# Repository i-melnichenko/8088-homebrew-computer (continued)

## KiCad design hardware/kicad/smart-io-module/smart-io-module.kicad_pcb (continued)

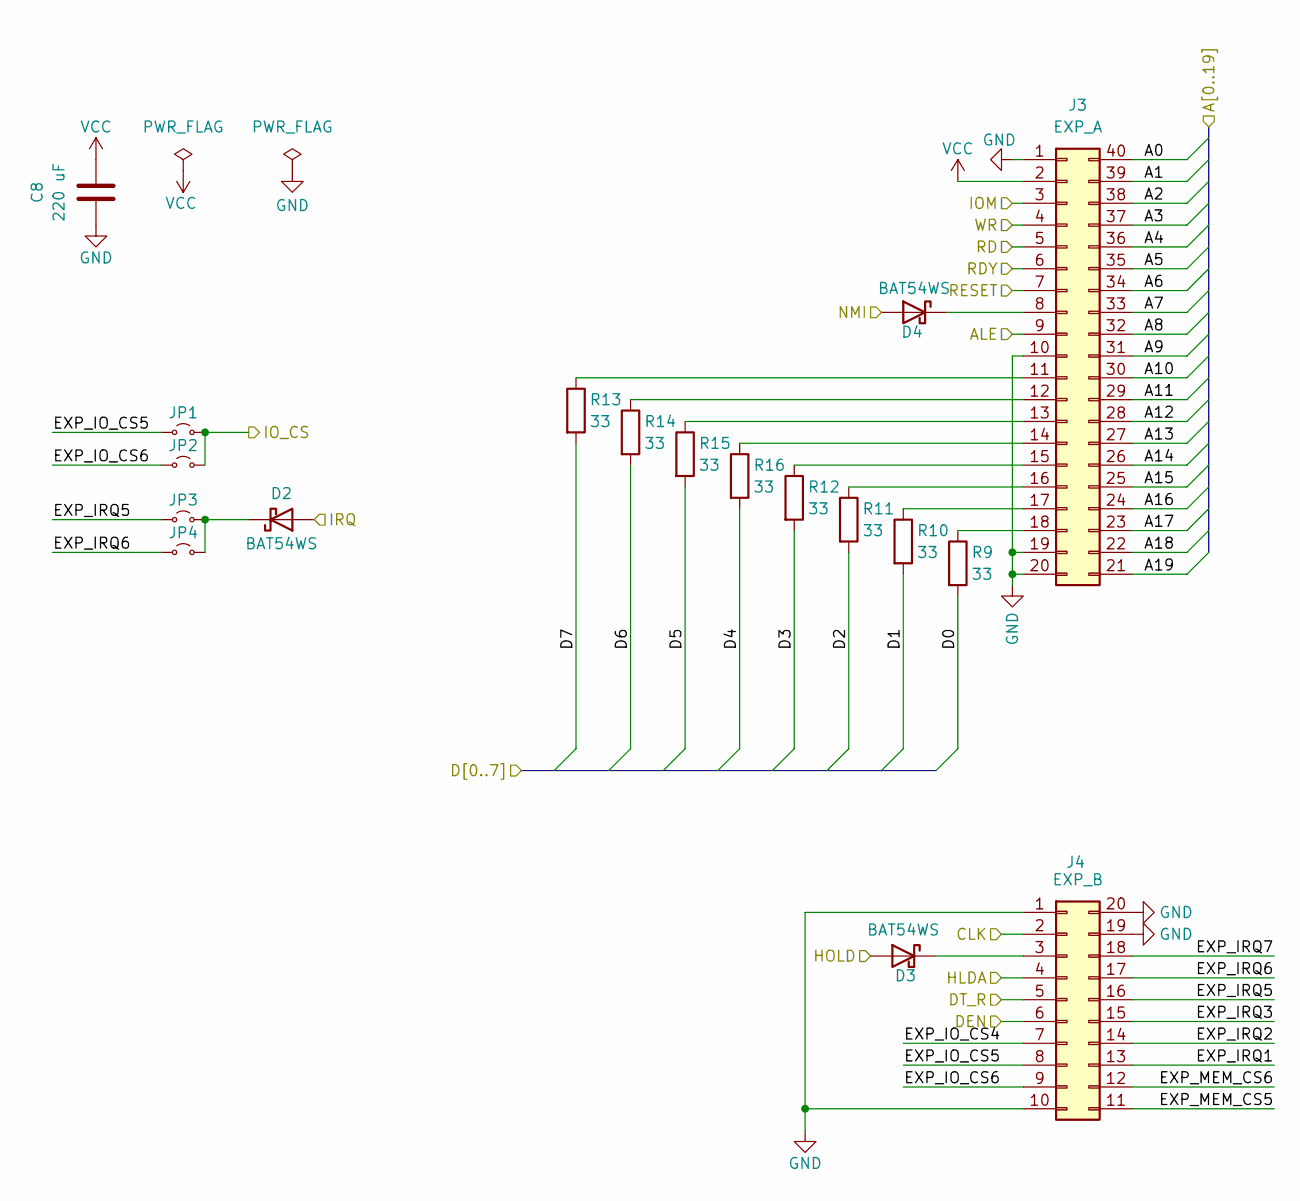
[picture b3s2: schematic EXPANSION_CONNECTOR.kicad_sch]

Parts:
C8: 220 uF; CP_Radial_D5.0mm_P2.00mm
D2, D3, D4: BAT54WS; D_SOD-323
J3: EXP_A; PinHeader_2x20_P2.54mm_Horizontal
J4: EXP_B; PinHeader_2x10_P2.54mm_Horizontal
JP1, JP2, JP3, JP4: Jumper_2_Small_Open; SolderJumper-2_P1.3mm_Open_Pad1.0x1.5mm
R9, R10, R11, R12, R13, R14, R15, R16: 33; R_0805_2012Metric

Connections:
/A0: J3.40; also elsewhere on the board
/A1: J3.39; also elsewhere on the board
/A2: J3.38; also elsewhere on the board
/A3: J3.37
/A4: J3.36
/A5: J3.35
/A6: J3.34
/A7: J3.33
/A8: J3.32
/A9: J3.31
/A10: J3.30
/A11: J3.29
/A12: J3.28
/A13: J3.27
/A14: J3.26
/A15: J3.25
/A16: J3.24
/A17: J3.23
/A18: J3.22
/A19: J3.21
/D0: R9.2; also elsewhere on the board
/D1: R10.2; also elsewhere on the board
/D2: R11.2; also elsewhere on the board
/D3: R12.2; also elsewhere on the board
/D4: R16.2; also elsewhere on the board
/D5: R15.2; also elsewhere on the board
/D6: R14.2; also elsewhere on the board
/D7: R13.2; also elsewhere on the board
/EXPANSION CONNECTOR/ALE: J3.9
/EXPANSION CONNECTOR/CLK: J4.2
/EXPANSION CONNECTOR/DEN: J4.6
/EXPANSION CONNECTOR/DT_R: J4.5
/EXPANSION CONNECTOR/EXP_IO_CS4: J4.7
/EXPANSION CONNECTOR/EXP_IO_CS5: J4.8, JP1.1 (A)
/EXPANSION CONNECTOR/EXP_IO_CS6: J4.9, JP2.1 (A)
/EXPANSION CONNECTOR/EXP_IRQ1: J4.13
/EXPANSION CONNECTOR/EXP_IRQ2: J4.14
/EXPANSION CONNECTOR/EXP_IRQ3: J4.15
/EXPANSION CONNECTOR/EXP_IRQ5: J4.16, JP3.1 (A)
/EXPANSION CONNECTOR/EXP_IRQ6: J4.17, JP4.1 (A)
/EXPANSION CONNECTOR/EXP_IRQ7: J4.18
/EXPANSION CONNECTOR/EXP_MEM_CS5: J4.11
/EXPANSION CONNECTOR/EXP_MEM_CS6: J4.12
/EXPANSION CONNECTOR/HOLD: D3.2 (A); also elsewhere on the board
/EXPANSION CONNECTOR/IOM: J3.3
/EXPANSION CONNECTOR/IRQ: D2.2 (A); also elsewhere on the board
/EXPANSION CONNECTOR/NMI: D4.2 (A); also elsewhere on the board
/EXPANSION CONNECTOR/RDY: J3.6
/HLDA: J4.4; also elsewhere on the board
/IO_CS: JP1.2 (B), JP2.2 (B); also elsewhere on the board
/RD: J3.5; also elsewhere on the board
/RESET: J3.7; also elsewhere on the board
/WR: J3.4; also elsewhere on the board
GND: C8.2, J3.1, J3.10, J3.19, J3.20, J4.1, J4.10, J4.19, J4.20; also elsewhere on the board
unnamed: D2.1 (K), JP3.2 (B), JP4.2 (B)
unnamed: D3.1 (K), J4.3
unnamed: D4.1 (K), J3.8
unnamed: J3.11, R13.1
unnamed: J3.12, R14.1
unnamed: J3.13, R15.1
unnamed: J3.14, R16.1
unnamed: J3.15, R12.1
unnamed: J3.16, R11.1
unnamed: J3.17, R10.1
unnamed: J3.18, R9.1
VCC: C8.1, J3.2; also elsewhere on the board

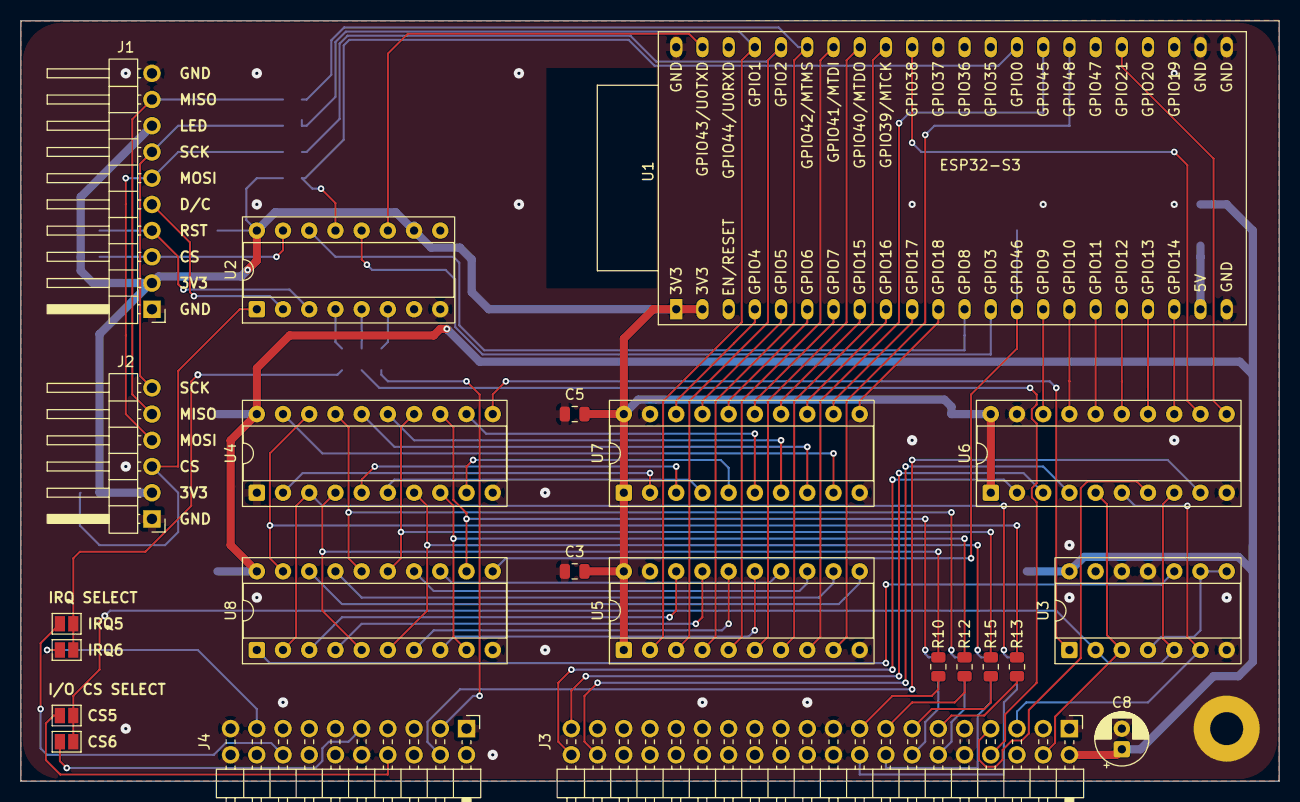
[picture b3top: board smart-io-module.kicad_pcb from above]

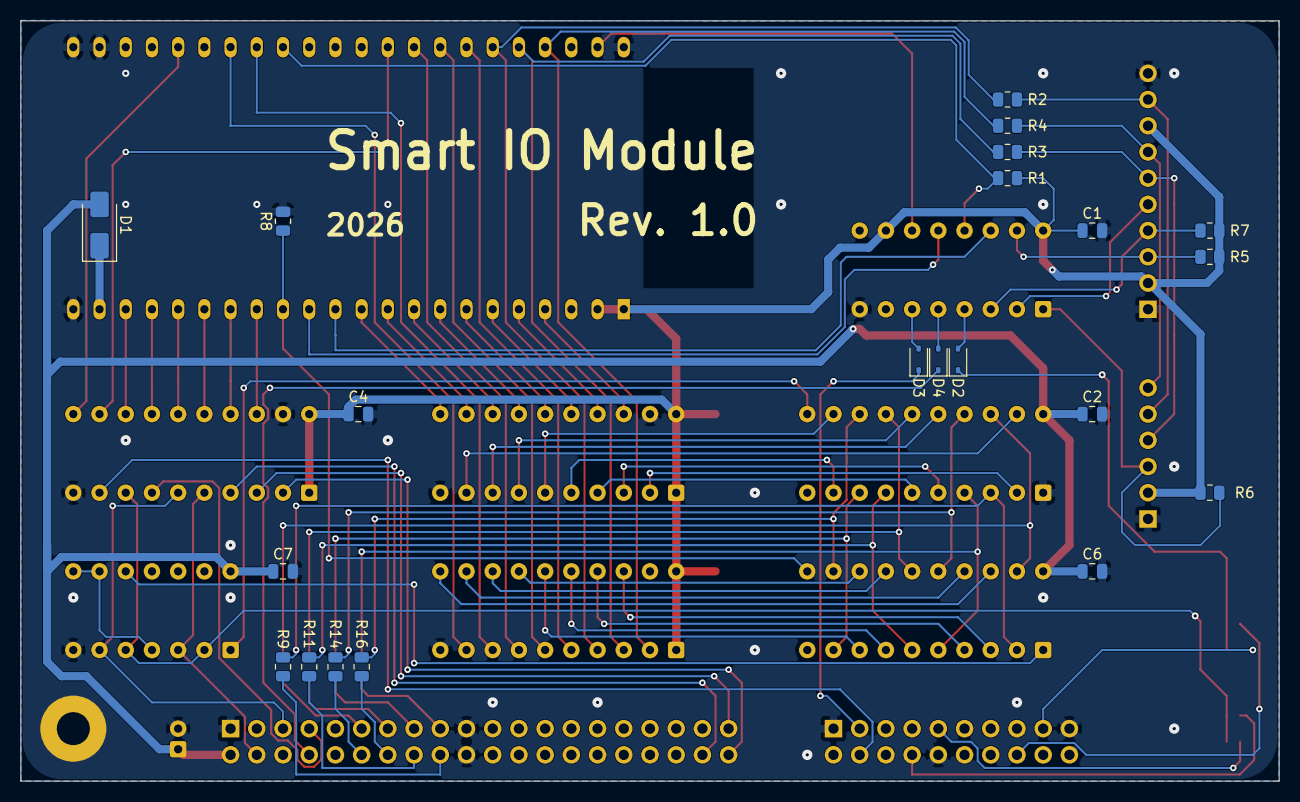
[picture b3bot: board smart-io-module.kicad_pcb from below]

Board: 2 copper layers, 121.9 x 73.7 mm, 45 parts (21 on the bottom side), 93 nets.

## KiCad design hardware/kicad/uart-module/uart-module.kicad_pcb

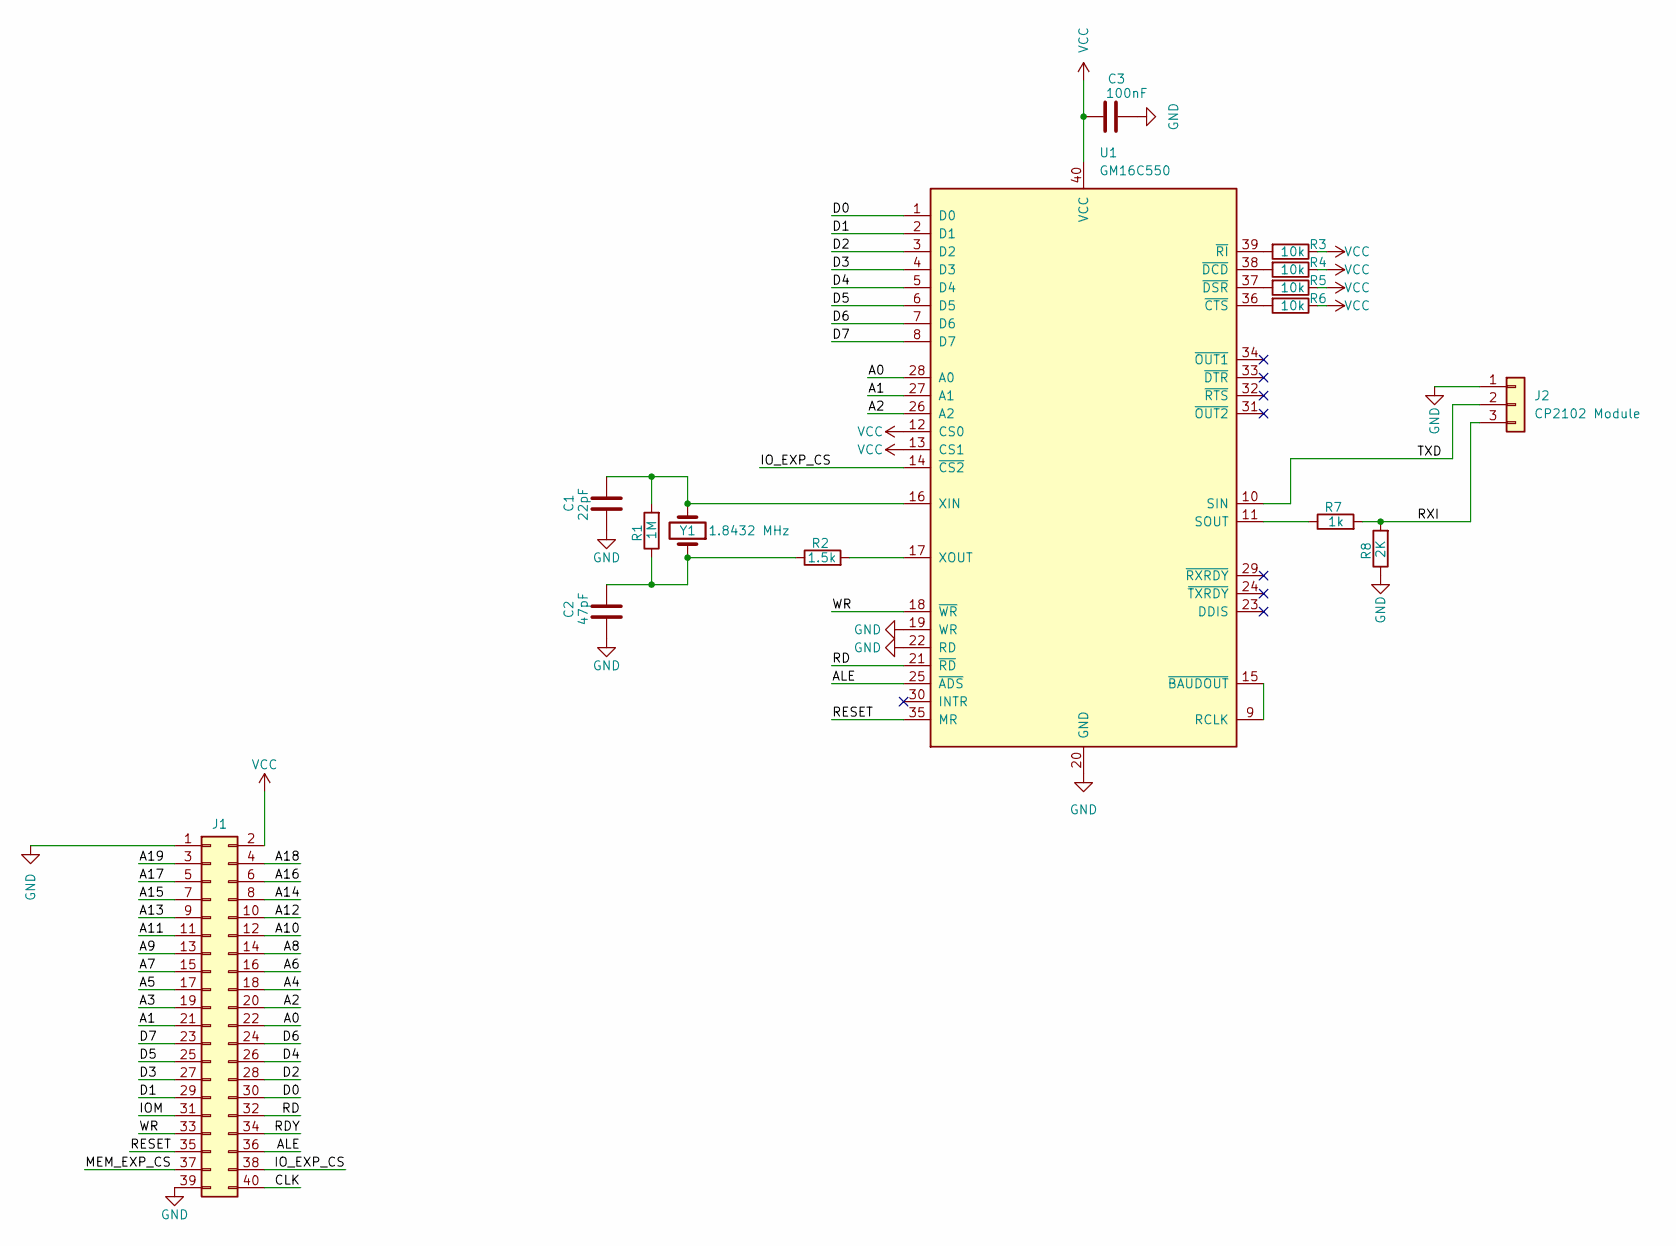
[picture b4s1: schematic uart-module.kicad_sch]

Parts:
C1: 22pF; C_Disc_D5.0mm_W2.5mm_P5.00mm
C2: 47pF; C_Disc_D5.0mm_W2.5mm_P5.00mm
C3: 100nF; C_Disc_D5.0mm_W2.5mm_P5.00mm
J1: Exp0; PinSocket_2x20_P2.54mm_Vertical
J2: CP2102 Module; PinHeader_1x03_P2.54mm_Vertical
R1: 1M; R_Axial_DIN0207_L6.3mm_D2.5mm_P7.62mm_Horizontal
R2: 1.5k; R_Axial_DIN0207_L6.3mm_D2.5mm_P7.62mm_Horizontal
R3, R4, R5, R6: 10k; R_Axial_DIN0207_L6.3mm_D2.5mm_P7.62mm_Horizontal
R7: 1k; R_Axial_DIN0207_L6.3mm_D2.5mm_P7.62mm_Horizontal
R8: 2K; R_Axial_DIN0207_L6.3mm_D2.5mm_P7.62mm_Horizontal
U1: GM16C550; DIP-40_W15.24mm
Y1: 1.8432 MHz; Crystal_HC49-U_Vertical

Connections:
/A0: J1.22, U1.28 (A0)
/A1: J1.21, U1.27 (A1)
/A2: J1.20, U1.26 (A2)
/A3: J1.19
/A4: J1.18
/A5: J1.17
/A6: J1.16
/A7: J1.15
/A8: J1.14
/A9: J1.13
/A10: J1.12
/A11: J1.11
/A12: J1.10
/A13: J1.9
/A14: J1.8
/A15: J1.7
/A16: J1.6
/A17: J1.5
/A18: J1.4
/A19: J1.3
/ALE: J1.36, U1.25 (~ADS)
/CLK: J1.40
/D0: J1.30, U1.1 (D0)
/D1: J1.29, U1.2 (D1)
/D2: J1.28, U1.3 (D2)
/D3: J1.27, U1.4 (D3)
/D4: J1.26, U1.5 (D4)
/D5: J1.25, U1.6 (D5)
/D6: J1.24, U1.7 (D6)
/D7: J1.23, U1.8 (D7)
/IOM: J1.31
/IO_EXP_CS: J1.38, U1.14 (~CS2)
/MEM_EXP_CS: J1.37
/RD: J1.32, U1.21 (~RD)
/RDY: J1.34
/RESET: J1.35, U1.35 (MR)
/RXI: J2.3, R7.2, R8.2
/TXD: J2.2, U1.10 (SIN)
/WR: J1.33, U1.18 (~WR)
GND: C1.1, C2.1, C3.2, J1.1, J1.39, J2.1, R8.1, U1.19 (WR), U1.20 (GND), U1.22 (RD)
unnamed: C2.2, R1.1, R2.1, Y1.1
unnamed: U1.9 (RCLK), U1.15 (~BAUDOUT)
unnamed: R7.1, U1.11 (SOUT)
unnamed: C1.2, R1.2, U1.16 (XIN), Y1.2
unnamed: R2.2, U1.17 (XOUT)
unnamed: R6.2, U1.36 (~CTS)
unnamed: R4.2, U1.38 (~DCD)
unnamed: R5.2, U1.37 (~DSR)
unnamed: R3.2, U1.39 (~RI)
VCC: C3.1, J1.2, R3.1, R4.1, R5.1, R6.1, U1.12 (CS0), U1.13 (CS1), U1.40 (VCC)

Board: 2 copper layers, 15 parts (2 on the bottom side), 29 nets, no tracks yet.

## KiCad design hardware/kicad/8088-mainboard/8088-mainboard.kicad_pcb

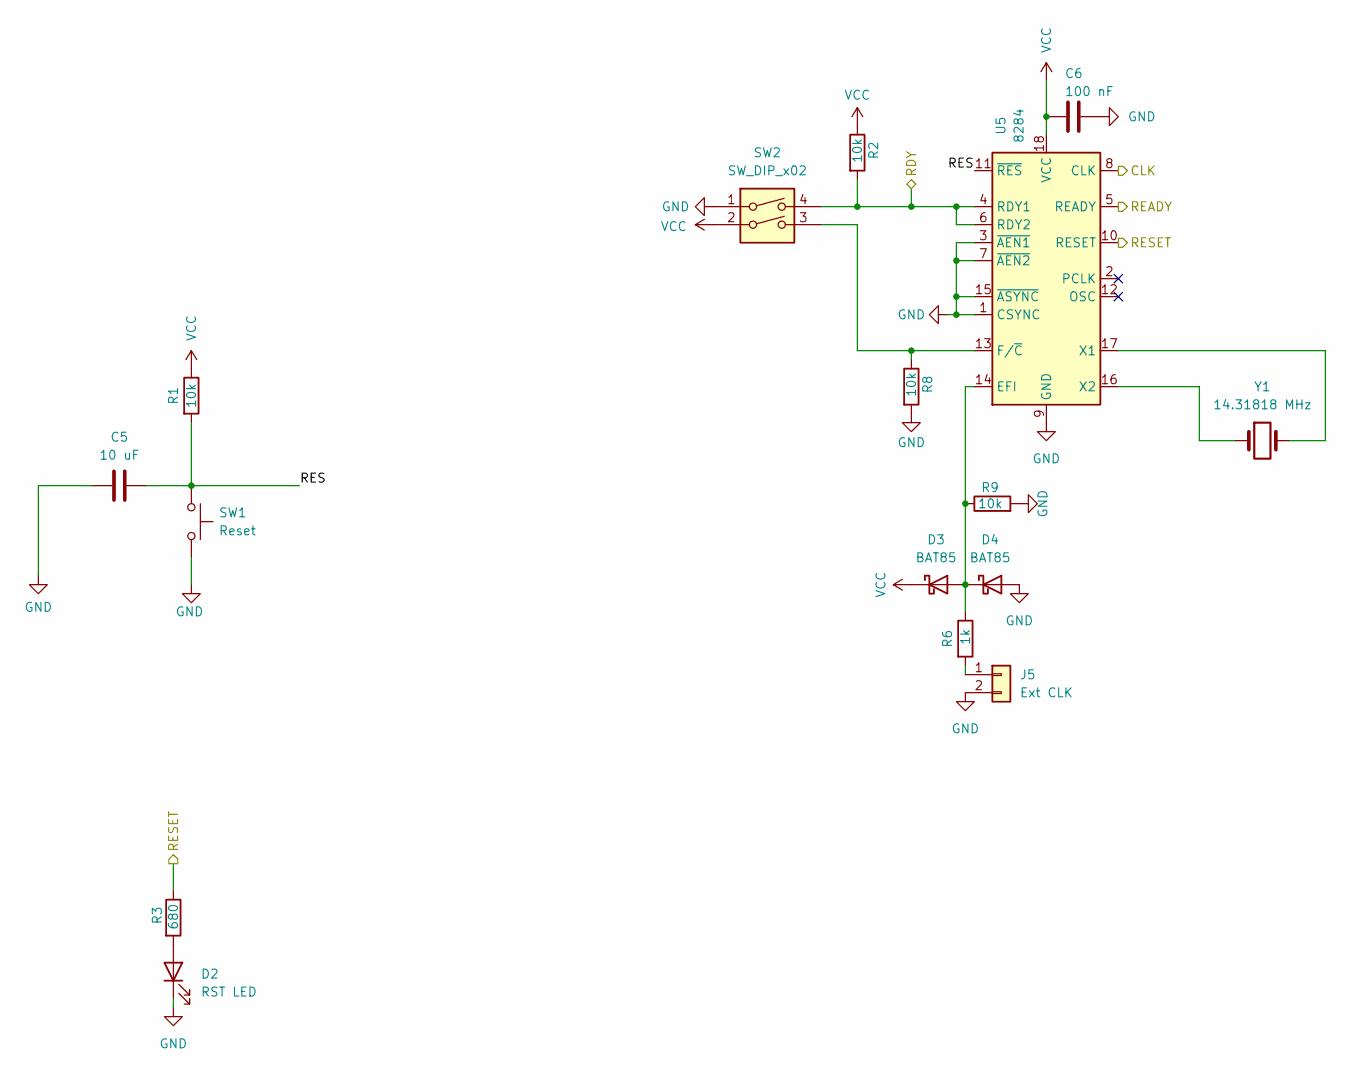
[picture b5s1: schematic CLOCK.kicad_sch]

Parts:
C5: 10 uF; CP_Radial_D4.0mm_P1.50mm
C6: 100 nF; C_Disc_D5.0mm_W2.5mm_P5.00mm
D2: RST LED; LED_D3.0mm
D3, D4: BAT85; D_DO-35_SOD27_P7.62mm_Horizontal
J5: Ext CLK; PinHeader_1x02_P2.54mm_Vertical
R1, R2, R8, R9: 10k; R_Axial_DIN0207_L6.3mm_D2.5mm_P7.62mm_Horizontal
R3: 680; R_Axial_DIN0207_L6.3mm_D2.5mm_P7.62mm_Horizontal
R6: 1k; R_Axial_DIN0207_L6.3mm_D2.5mm_P7.62mm_Horizontal
SW1: Reset; SW_PUSH_6mm
SW2: SW_DIP_x02; SW_DIP_SPSTx02_Slide_9.78x7.26mm_W7.62mm_P2.54mm
U5: 8284; DIP-18_W7.62mm_Socket
Y1: 14.31818 MHz; Crystal_HC49-U_Vertical

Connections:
/CLK: U5.8 (CLK); also elsewhere on the board
/CLOCK/RES: C5.1, R1.2, SW1.1, U5.11 (~RES)
/RDY: R2.2, SW2.4, U5.4 (RDY1), U5.6 (RDY2); also elsewhere on the board
/READY: U5.5 (READY); also elsewhere on the board
/RESET: R3.1, U5.10 (RESET); also elsewhere on the board
GND: C5.2, C6.2, D2.1 (K), D4.2 (A), J5.2, R8.2, R9.2, SW1.2, SW2.1, U5.1 (CSYNC), U5.3 (~AEN1), U5.7 (~AEN2), U5.9 (GND), U5.15 (~ASYNC); also elsewhere on the board
unnamed: D2.2 (A), R3.2
unnamed: D3.2 (A), D4.1 (K), R6.1, R9.1, U5.14 (EFI)
unnamed: J5.1, R6.2
unnamed: R8.1, SW2.3, U5.13 (F/~C)
unnamed: U5.17 (X1), Y1.2
unnamed: U5.16 (X2), Y1.1
VCC: C6.1, D3.1 (K), R1.1, R2.1, SW2.2, U5.18 (VCC); also elsewhere on the board

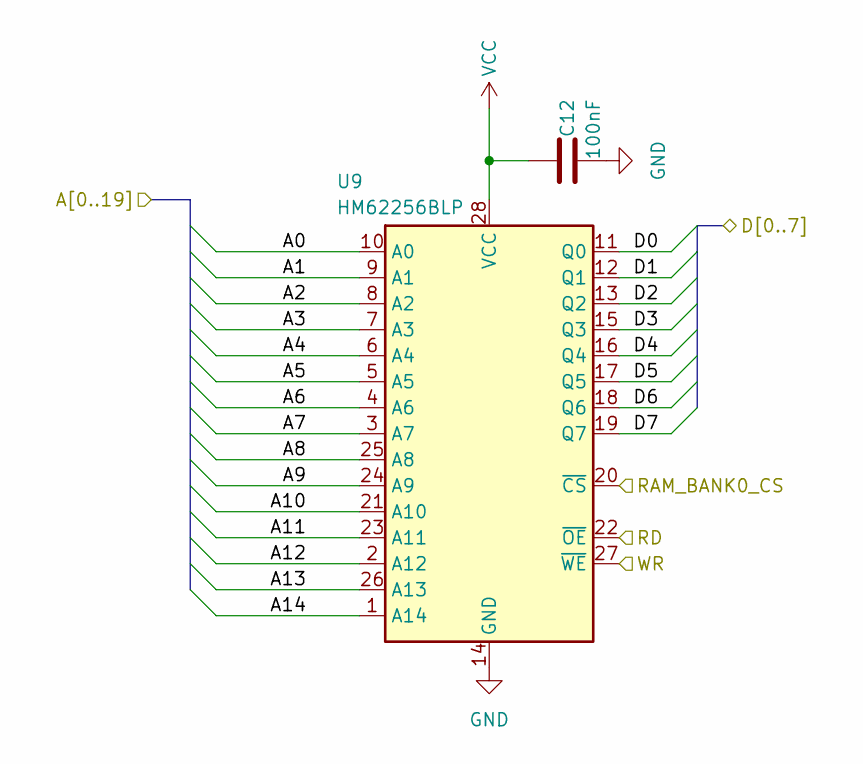
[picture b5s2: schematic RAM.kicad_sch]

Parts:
C12: 100nF; C_Disc_D5.0mm_W2.5mm_P5.00mm
U9: HM62256BLP; DIP-28_W15.24mm_Socket

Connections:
/A0: U9.10 (A0); also elsewhere on the board
/A1: U9.9 (A1); also elsewhere on the board
/A2: U9.8 (A2); also elsewhere on the board
/A3: U9.7 (A3); also elsewhere on the board
/A4: U9.6 (A4); also elsewhere on the board
/A5: U9.5 (A5); also elsewhere on the board
/A6: U9.4 (A6); also elsewhere on the board
/A7: U9.3 (A7); also elsewhere on the board
/A8: U9.25 (A8); also elsewhere on the board
/A9: U9.24 (A9); also elsewhere on the board
/A10: U9.21 (A10); also elsewhere on the board
/A11: U9.23 (A11); also elsewhere on the board
/A12: U9.2 (A12); also elsewhere on the board
/A13: U9.26 (A13); also elsewhere on the board
/A14: U9.1 (A14); also elsewhere on the board
/D0: U9.11 (Q0); also elsewhere on the board
/D1: U9.12 (Q1); also elsewhere on the board
/D2: U9.13 (Q2); also elsewhere on the board
/D3: U9.15 (Q3); also elsewhere on the board
/D4: U9.16 (Q4); also elsewhere on the board
/D5: U9.17 (Q5); also elsewhere on the board
/D6: U9.18 (Q6); also elsewhere on the board
/D7: U9.19 (Q7); also elsewhere on the board
/MEM_DECODER/RAM_BANK0_CS: U9.20 (~CS); also elsewhere on the board
/RD: U9.22 (~OE); also elsewhere on the board
/WR: U9.27 (~WE); also elsewhere on the board
GND: C12.2, U9.14 (GND); also elsewhere on the board
VCC: C12.1, U9.28 (VCC); also elsewhere on the board

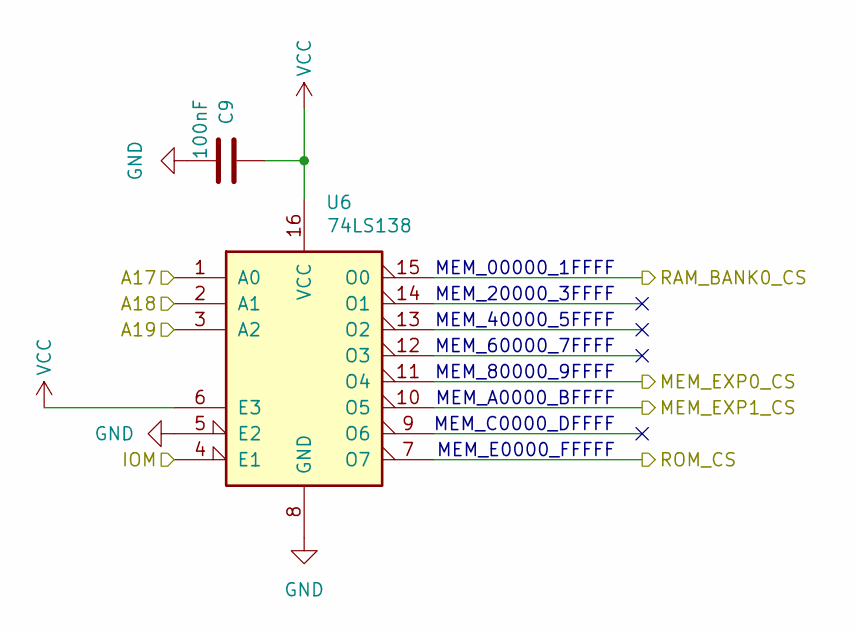
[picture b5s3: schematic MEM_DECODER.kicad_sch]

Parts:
C9: 100nF; C_Disc_D5.0mm_W2.5mm_P5.00mm
U6: 74LS138; DIP-16_W7.62mm_Socket

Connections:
/A17: U6.1 (A0); also elsewhere on the board
/A18: U6.2 (A1); also elsewhere on the board
/A19: U6.3 (A2); also elsewhere on the board
/EXPANSION_CONNECTOR/MEM_EXP0_CS: U6.11 (O4); also elsewhere on the board
/EXPANSION_CONNECTOR/MEM_EXP1_CS: U6.10 (O5); also elsewhere on the board
/IOM: U6.4 (E1); also elsewhere on the board
/MEM_DECODER/RAM_BANK0_CS: U6.15 (O0); also elsewhere on the board
/MEM_DECODER/ROM_CS: U6.7 (O7); also elsewhere on the board
GND: C9.2, U6.5 (E2), U6.8 (GND); also elsewhere on the board
VCC: C9.1, U6.6 (E3), U6.16 (VCC); also elsewhere on the board

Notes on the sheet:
MEM_80000_9FFFF
MEM_60000_7FFFF
MEM_20000_3FFFF
MEM_E0000_FFFFF
MEM_40000_5FFFF
MEM_A0000_BFFFF
MEM_00000_1FFFF
MEM_C0000_DFFFF

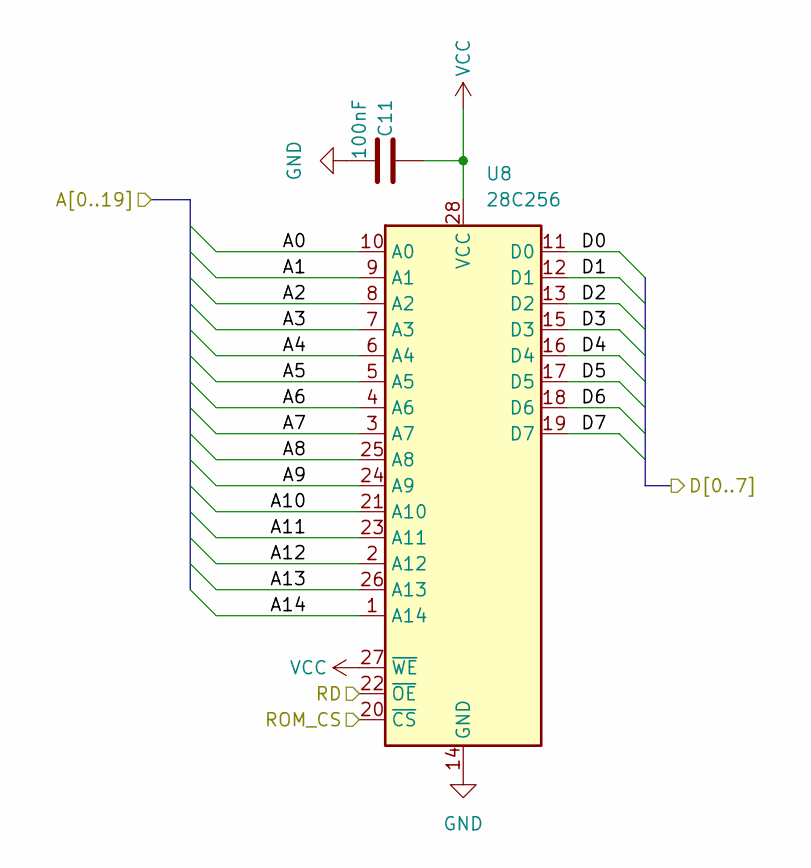
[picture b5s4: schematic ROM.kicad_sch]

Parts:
C11: 100nF; C_Disc_D5.0mm_W2.5mm_P5.00mm
U8: 28C256; DIP_Socket-28_W11.9mm_W12.7mm_W15.24mm_W17.78mm_W18.5mm_3M_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

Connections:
/A0: U8.10 (A0); also elsewhere on the board
/A1: U8.9 (A1); also elsewhere on the board
/A2: U8.8 (A2); also elsewhere on the board
/A3: U8.7 (A3); also elsewhere on the board
/A4: U8.6 (A4); also elsewhere on the board
/A5: U8.5 (A5); also elsewhere on the board
/A6: U8.4 (A6); also elsewhere on the board
/A7: U8.3 (A7); also elsewhere on the board
/A8: U8.25 (A8); also elsewhere on the board
/A9: U8.24 (A9); also elsewhere on the board
/A10: U8.21 (A10); also elsewhere on the board
/A11: U8.23 (A11); also elsewhere on the board
/A12: U8.2 (A12); also elsewhere on the board
/A13: U8.26 (A13); also elsewhere on the board
/A14: U8.1 (A14); also elsewhere on the board
/D0: U8.11 (D0); also elsewhere on the board
/D1: U8.12 (D1); also elsewhere on the board
/D2: U8.13 (D2); also elsewhere on the board
/D3: U8.15 (D3); also elsewhere on the board
/D4: U8.16 (D4); also elsewhere on the board
/D5: U8.17 (D5); also elsewhere on the board
/D6: U8.18 (D6); also elsewhere on the board
/D7: U8.19 (D7); also elsewhere on the board
/MEM_DECODER/ROM_CS: U8.20 (~CS); also elsewhere on the board
/RD: U8.22 (~OE); also elsewhere on the board
GND: C11.2, U8.14 (GND); also elsewhere on the board
VCC: C11.1, U8.27 (~WE), U8.28 (VCC); also elsewhere on the board

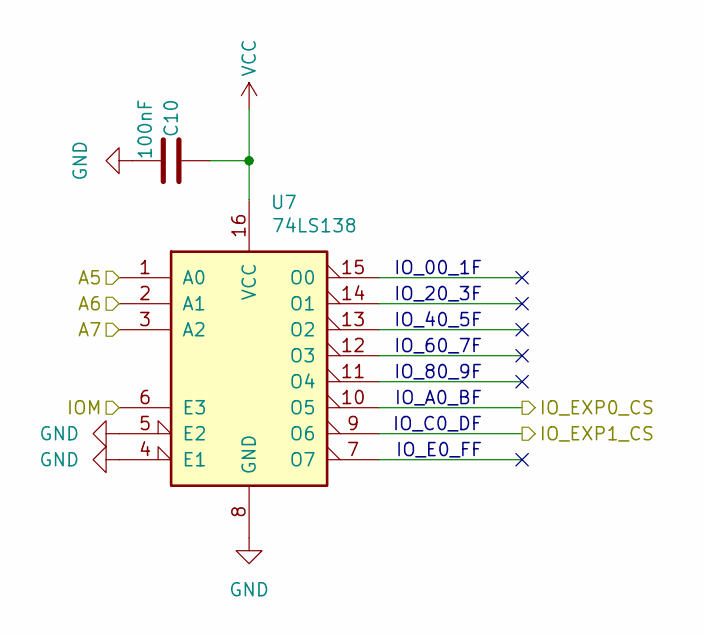
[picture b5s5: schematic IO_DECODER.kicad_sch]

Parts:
C10: 100nF; C_Disc_D5.0mm_W2.5mm_P5.00mm
U7: 74LS138; DIP-16_W7.62mm_Socket

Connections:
/A5: U7.1 (A0); also elsewhere on the board
/A6: U7.2 (A1); also elsewhere on the board
/A7: U7.3 (A2); also elsewhere on the board
/EXPANSION_CONNECTOR/IO_EXP0_CS: U7.10 (O5); also elsewhere on the board
/EXPANSION_CONNECTOR/IO_EXP1_CS: U7.9 (O6); also elsewhere on the board
/IOM: U7.6 (E3); also elsewhere on the board
GND: C10.2, U7.4 (E1), U7.5 (E2), U7.8 (GND); also elsewhere on the board
VCC: C10.1, U7.16 (VCC); also elsewhere on the board

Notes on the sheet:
IO_A0_BF
IO_20_3F
IO_60_7F
IO_C0_DF
IO_00_1F
IO_E0_FF
IO_40_5F
IO_80_9F

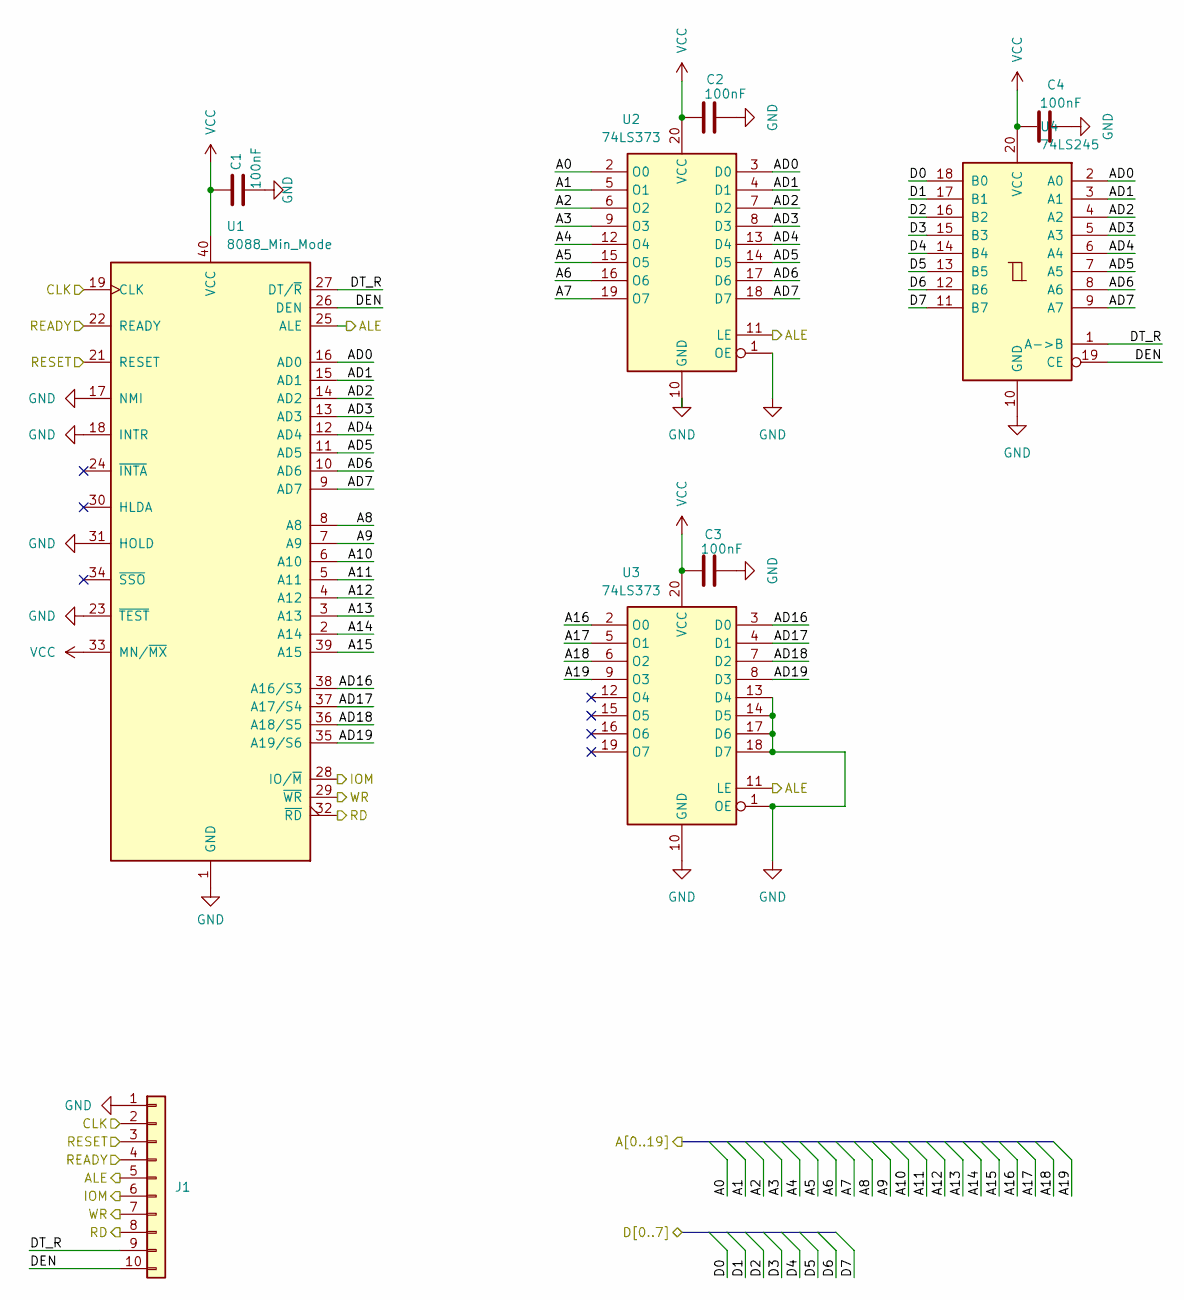
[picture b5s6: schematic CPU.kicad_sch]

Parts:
C1, C2, C3, C4: 100nF; C_Disc_D5.0mm_W2.5mm_P5.00mm
J1: Conn_01x10; PinHeader_1x10_P2.54mm_Vertical
U1: 8088_Min_Mode; DIP-40_W15.24mm_Socket
U2, U3: 74LS373; DIP-20_W7.62mm_Socket
U4: 74LS245; DIP-20_W7.62mm_Socket

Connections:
/A0: U2.2 (O0); also elsewhere on the board
/A1: U2.5 (O1); also elsewhere on the board
/A2: U2.6 (O2); also elsewhere on the board
/A3: U2.9 (O3); also elsewhere on the board
/A4: U2.12 (O4); also elsewhere on the board
/A5: U2.15 (O5); also elsewhere on the board
/A6: U2.16 (O6); also elsewhere on the board
/A7: U2.19 (O7); also elsewhere on the board
/A8: U1.8 (A8); also elsewhere on the board
/A9: U1.7 (A9); also elsewhere on the board
/A10: U1.6 (A10); also elsewhere on the board
/A11: U1.5 (A11); also elsewhere on the board
/A12: U1.4 (A12); also elsewhere on the board
/A13: U1.3 (A13); also elsewhere on the board
/A14: U1.2 (A14); also elsewhere on the board
/A15: U1.39 (A15); also elsewhere on the board
/A16: U3.2 (O0); also elsewhere on the board
/A17: U3.5 (O1); also elsewhere on the board
/A18: U3.6 (O2); also elsewhere on the board
/A19: U3.9 (O3); also elsewhere on the board
/ALE: J1.5, U1.25 (ALE), U2.11 (LE), U3.11 (LE); also elsewhere on the board
/CLK: J1.2, U1.19 (CLK); also elsewhere on the board
/CPU/AD0: U1.16 (AD0), U2.3 (D0), U4.2 (A0)
/CPU/AD1: U1.15 (AD1), U2.4 (D1), U4.3 (A1)
/CPU/AD2: U1.14 (AD2), U2.7 (D2), U4.4 (A2)
/CPU/AD3: U1.13 (AD3), U2.8 (D3), U4.5 (A3)
/CPU/AD4: U1.12 (AD4), U2.13 (D4), U4.6 (A4)
/CPU/AD5: U1.11 (AD5), U2.14 (D5), U4.7 (A5)
/CPU/AD6: U1.10 (AD6), U2.17 (D6), U4.8 (A6)
/CPU/AD7: U1.9 (AD7), U2.18 (D7), U4.9 (A7)
/CPU/AD16: U1.38 (A16/S3), U3.3 (D0)
/CPU/AD17: U1.37 (A17/S4), U3.4 (D1)
/CPU/AD18: U1.36 (A18/S5), U3.7 (D2)
/CPU/AD19: U1.35 (A19/S6), U3.8 (D3)
/CPU/DEN: J1.10, U1.26 (DEN), U4.19 (CE)
/CPU/DT_R: J1.9, U1.27 (DT/~R), U4.1 (A->B)
/D0: U4.18 (B0); also elsewhere on the board
/D1: U4.17 (B1); also elsewhere on the board
/D2: U4.16 (B2); also elsewhere on the board
/D3: U4.15 (B3); also elsewhere on the board
/D4: U4.14 (B4); also elsewhere on the board
/D5: U4.13 (B5); also elsewhere on the board
/D6: U4.12 (B6); also elsewhere on the board
/D7: U4.11 (B7); also elsewhere on the board
/IOM: J1.6, U1.28 (IO/~M); also elsewhere on the board
/RD: J1.8, U1.32 (~RD); also elsewhere on the board
/READY: J1.4, U1.22 (READY); also elsewhere on the board
/RESET: J1.3, U1.21 (RESET); also elsewhere on the board
/WR: J1.7, U1.29 (~WR); also elsewhere on the board
GND: C1.2, C2.2, C3.2, C4.2, J1.1, U1.1 (GND), U1.17 (NMI), U1.18 (INTR), U1.20 (GND), U1.23 (~TEST), U1.31 (HOLD), U2.1 (OE), U2.10 (GND), U3.1 (OE), U3.10 (GND), U3.13 (D4), U3.14 (D5), U3.17 (D6), U3.18 (D7), U4.10 (GND); also elsewhere on the board
VCC: C1.1, C2.1, C3.1, C4.1, U1.33 (MN/~MX), U1.40 (VCC), U2.20 (VCC), U3.20 (VCC), U4.20 (VCC); also elsewhere on the board

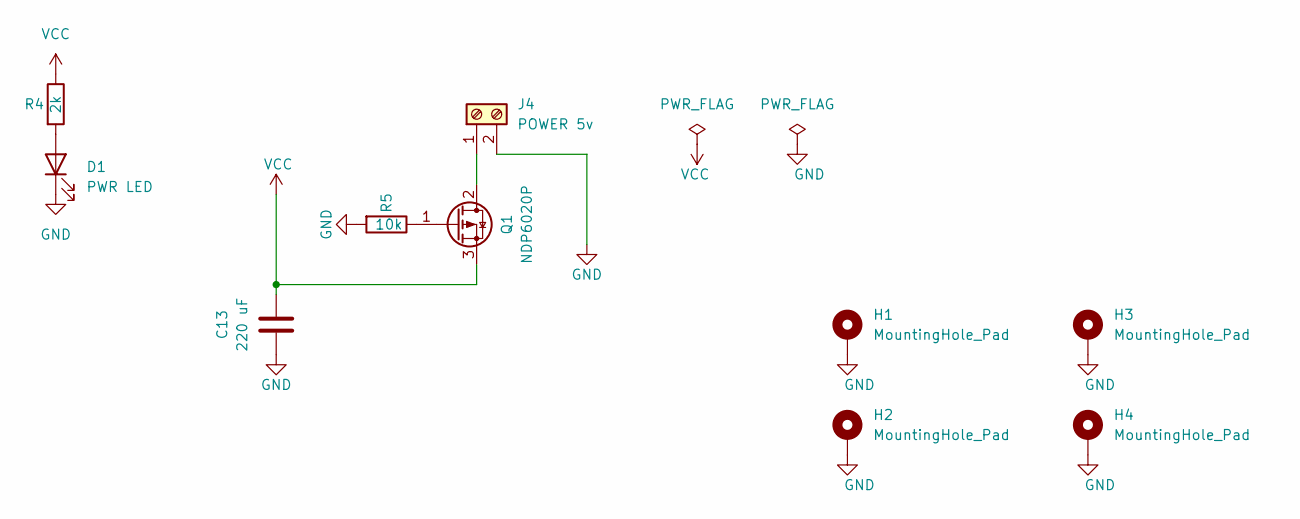
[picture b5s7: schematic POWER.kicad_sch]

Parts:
C13: 220 uF; CP_Radial_D5.0mm_P2.00mm
D1: PWR LED; LED_D3.0mm
H1, H2, H3, H4: MountingHole_Pad; MountingHole_3.2mm_M3_Pad
J4: POWER 5v; TerminalBlock_Phoenix_MKDS-1,5-2-5.08_1x02_P5.08mm_Horizont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
Q1: NDP6020P; TO-220-3_Horizontal_TabDown
R4: 2k; R_Axial_DIN0207_L6.3mm_D2.5mm_P7.62mm_Horizontal
R5: 10k; R_Axial_DIN0207_L6.3mm_D2.5mm_P7.62mm_Horizontal

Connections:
GND: C13.2, D1.1 (K), H1.1 (1_1), H2.1 (1_1), H3.1 (1_1), H4.1 (1_1), J4.2, R5.2; also elsewhere on the board
unnamed: D1.2 (A), R4.2
unnamed: J4.1, Q1.2 (D)
unnamed: Q1.1 (G), R5.1
VCC: C13.1, Q1.3 (S), R4.1; also elsewhere on the board

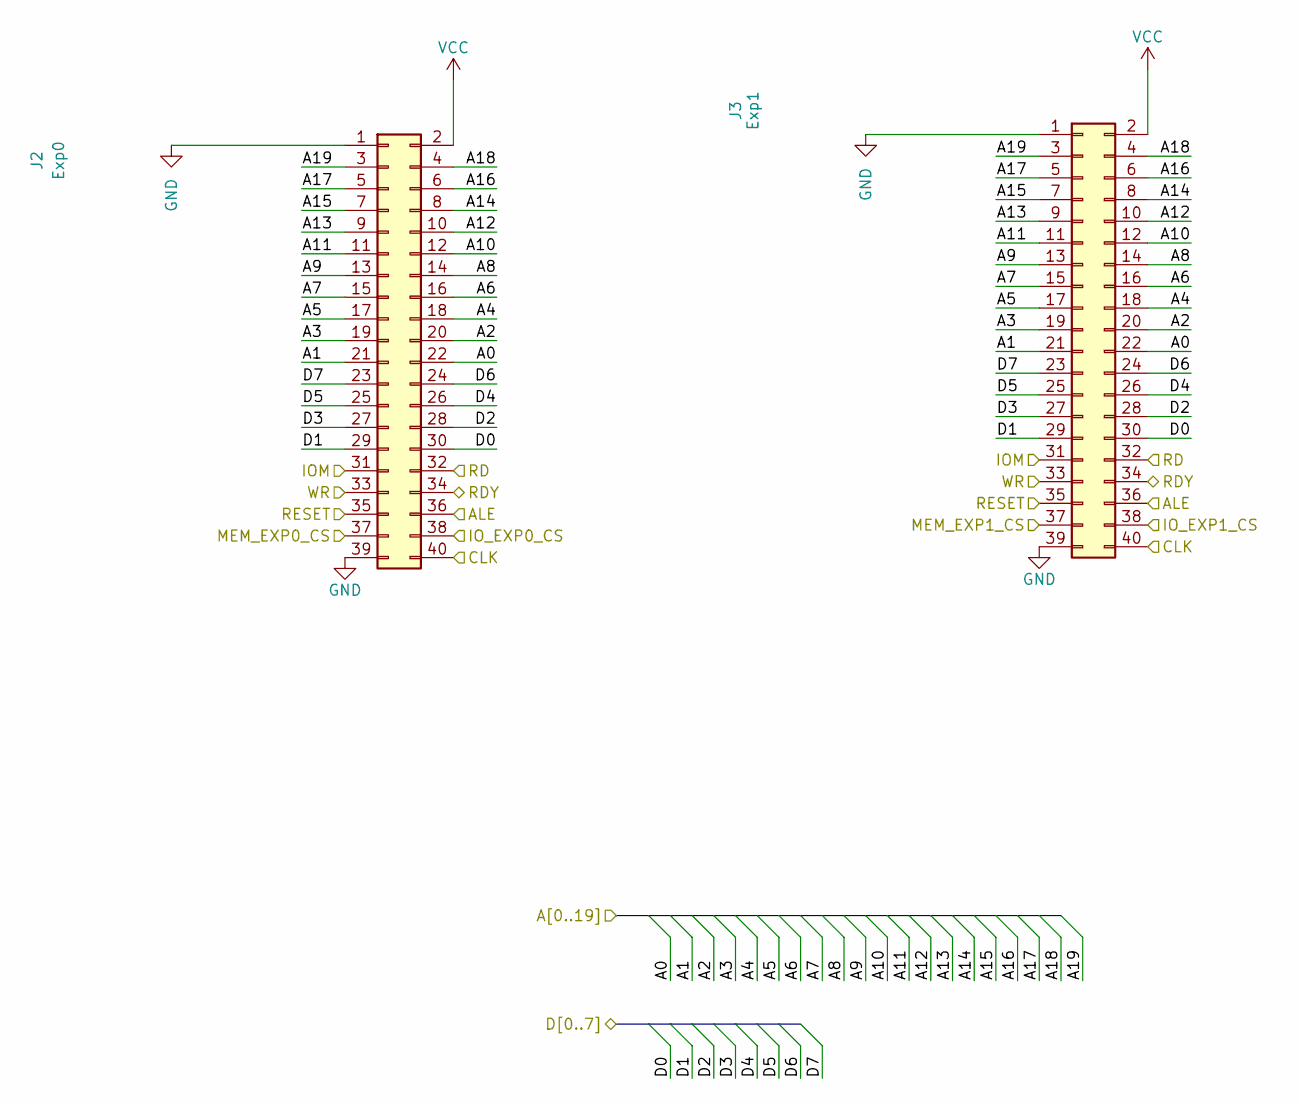
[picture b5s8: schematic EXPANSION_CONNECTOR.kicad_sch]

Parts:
J2: Exp0; IDC-Header_2x20_P2.54mm_Vertical
J3: Exp1; IDC-Header_2x20_P2.54mm_Vertical

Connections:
/A0: J2.22, J3.22; also elsewhere on the board
/A1: J2.21, J3.21; also elsewhere on the board
/A2: J2.20, J3.20; also elsewhere on the board
/A3: J2.19, J3.19; also elsewhere on the board
/A4: J2.18, J3.18; also elsewhere on the board
/A5: J2.17, J3.17; also elsewhere on the board
/A6: J2.16, J3.16; also elsewhere on the board
/A7: J2.15, J3.15; also elsewhere on the board
/A8: J2.14, J3.14; also elsewhere on the board
/A9: J2.13, J3.13; also elsewhere on the board
/A10: J2.12, J3.12; also elsewhere on the board
/A11: J2.11, J3.11; also elsewhere on the board
/A12: J2.10, J3.10; also elsewhere on the board
/A13: J2.9, J3.9; also elsewhere on the board
/A14: J2.8, J3.8; also elsewhere on the board
/A15: J2.7, J3.7; also elsewhere on the board
/A16: J2.6, J3.6; also elsewhere on the board
/A17: J2.5, J3.5; also elsewhere on the board
/A18: J2.4, J3.4; also elsewhere on the board
/A19: J2.3, J3.3; also elsewhere on the board
/ALE: J2.36, J3.36; also elsewhere on the board
/CLK: J2.40, J3.40; also elsewhere on the board
/D0: J2.30, J3.30; also elsewhere on the board
/D1: J2.29, J3.29; also elsewhere on the board
/D2: J2.28, J3.28; also elsewhere on the board
/D3: J2.27, J3.27; also elsewhere on the board
/D4: J2.26, J3.26; also elsewhere on the board
/D5: J2.25, J3.25; also elsewhere on the board
/D6: J2.24, J3.24; also elsewhere on the board
/D7: J2.23, J3.23; also elsewhere on the board
/EXPANSION_CONNECTOR/IO_EXP0_CS: J2.38; also elsewhere on the board
/EXPANSION_CONNECTOR/IO_EXP1_CS: J3.38; also elsewhere on the board
/EXPANSION_CONNECTOR/MEM_EXP0_CS: J2.37; also elsewhere on the board
/EXPANSION_CONNECTOR/MEM_EXP1_CS: J3.37; also elsewhere on the board
/IOM: J2.31, J3.31; also elsewhere on the board
/RD: J2.32, J3.32; also elsewhere on the board
/RDY: J2.34, J3.34; also elsewhere on the board
/RESET: J2.35, J3.35; also elsewhere on the board
/WR: J2.33, J3.33; also elsewhere on the board
GND: J2.1, J2.39, J3.1, J3.39; also elsewhere on the board
VCC: J2.2, J3.2; also elsewhere on the board
